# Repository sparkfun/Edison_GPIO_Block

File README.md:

SparkFun Edison GPIO Breakout
=============================

[*SparkFun Edison GPIO Breakout(DEV-13038)*](https://www.sparkfun.com/products/13038)

The GPIO Breakout is a simple breakout board to bring the GPIO from the Intel Edison to the user.  Bread board friendly, the GPIO provides level-shifted access to all basic GPIO, PWM, and UART2. GPIO may be set to VSYS or 3.3v levels. The GPIO Breakout also provides access to all three power rails found on the Intel Edison.  3.3v, 1.8v, VSYS, and GND are accessable for bread board prototyping.

Repository Contents
-------------------
* **/Hardware** - All Eagle design files (.brd, .sch)
* **/Production** - TEst bed files and production panel files

License Information
-------------------

The hardware is released under [Creative Commons ShareAlike 4.0 International](https://creativecommons.org/licenses/by-sa/4.0/).
The code is beerware; if you see me (or any other SparkFun employee) at the local, and you've found our code helpful, please buy us a round!

Distributed as-is; no warranty is given.

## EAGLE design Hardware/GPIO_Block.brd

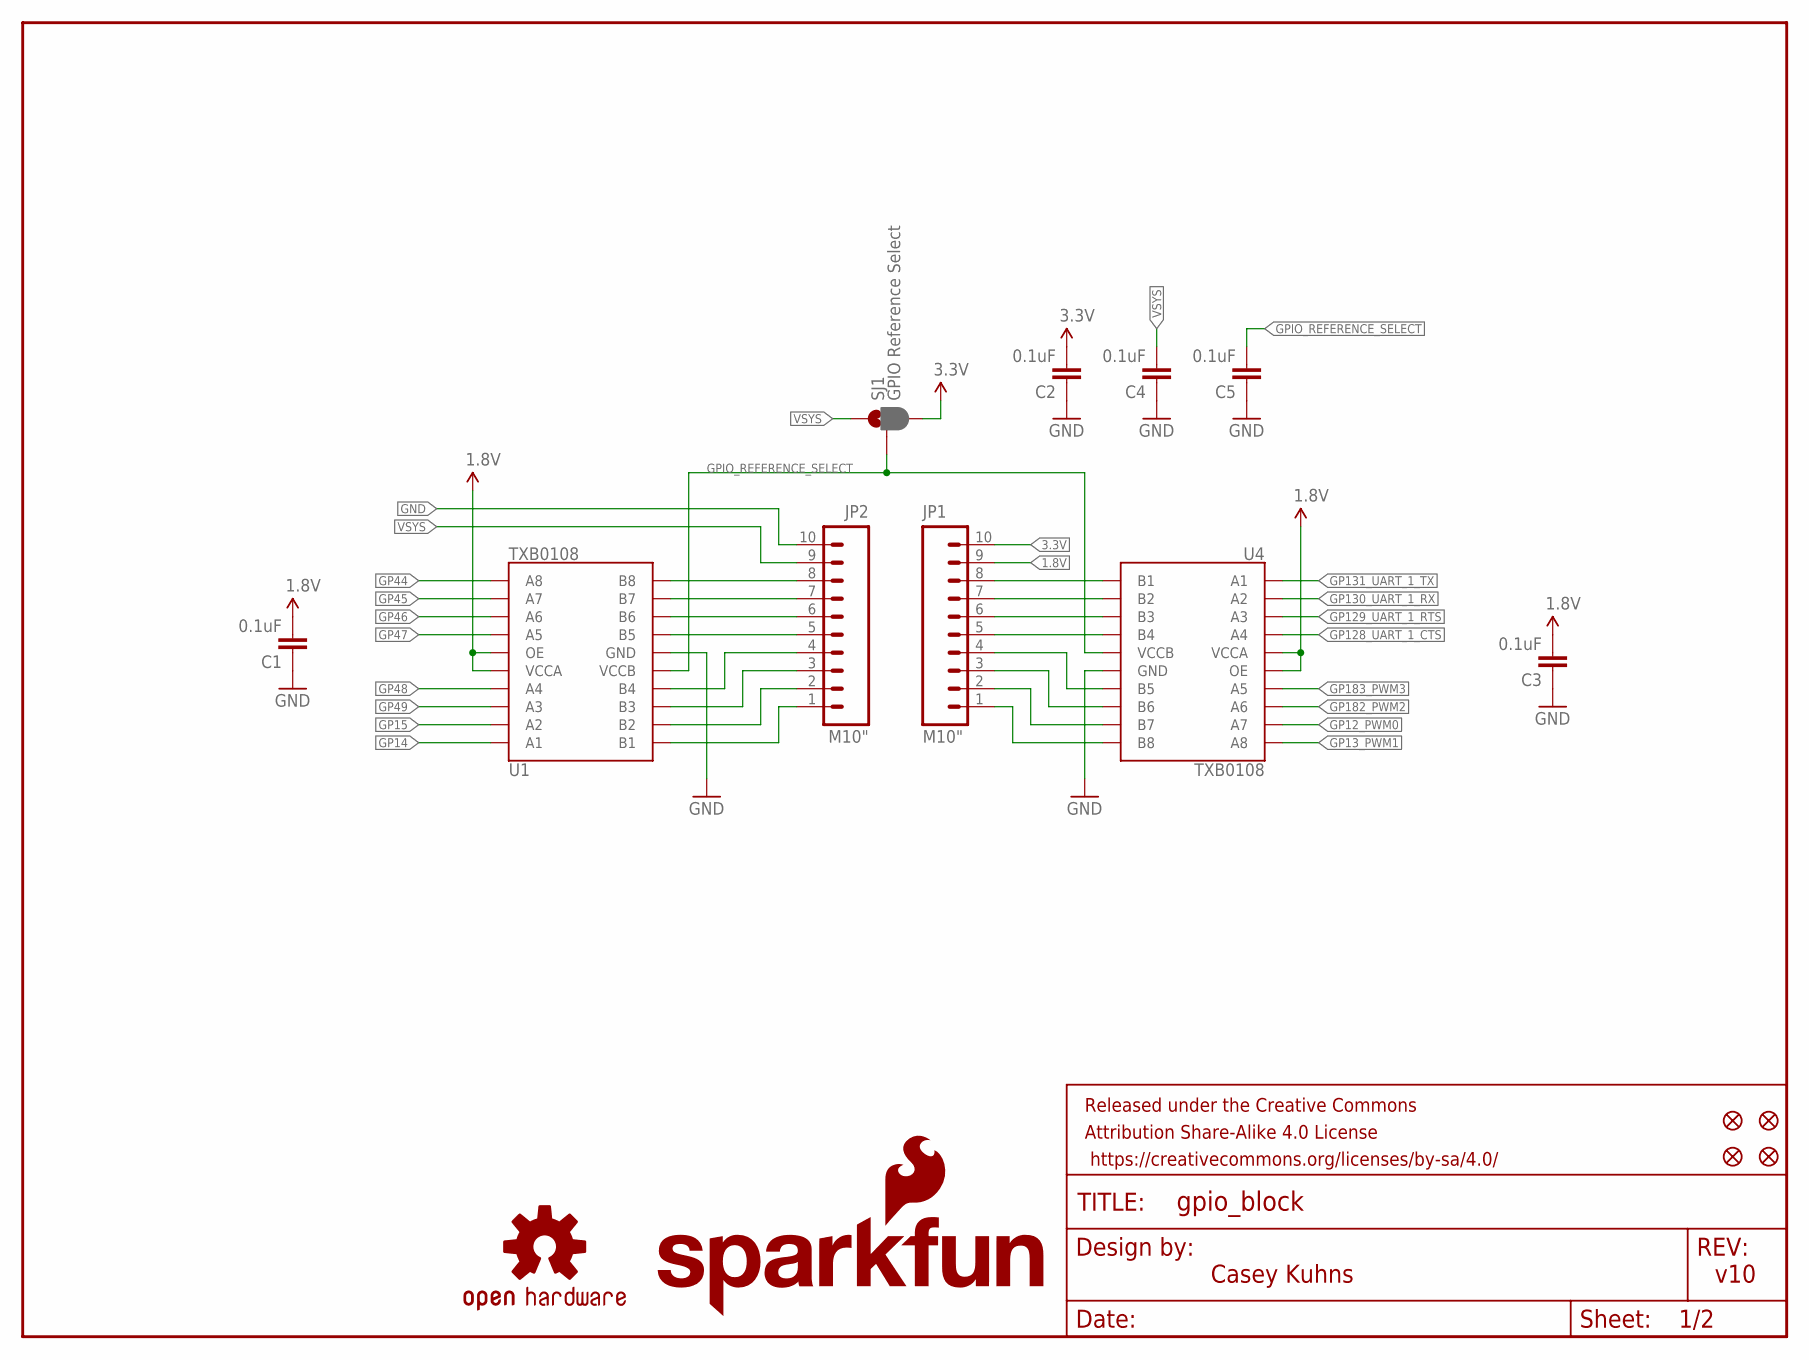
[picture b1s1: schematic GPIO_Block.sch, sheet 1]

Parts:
C1, C2, C3, C4, C5: 0.1uF; 0603-CAP
FID1, FID2, FID3, FID4: FIDUCIAL1X2; FIDUCIAL-1X2
FRAME1: FRAME-LETTER; CREATIVE_COMMONS
JP1, JP2: M10"; 1X10
LOGO1: OSHW-LOGOS; OSHW-LOGO-S
LOGO4: SFE_LOGO_NAME_FLAME.1_INCH; SFE_LOGO_NAME_FLAME_.1
SJ1: GPIO Reference Select; PAD-JUMPER-3-2OF3_NC_BY_PASTE_YES_SILK_FULL_BOX
U1, U4: TXB0108; UFDFN-20

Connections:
1.8V: C1.2, C3.2, JP1.9, U1.5 (VCCA), U1.6 (OE), U4.5 (VCCA), U4.6 (OE); also elsewhere on the board
3.3V: C2.2, JP1.10, SJ1.3; also elsewhere on the board
GND: C1.1, C2.1, C3.1, C4.1, C5.1, JP2.10, U1.15 (GND), U4.15 (GND); also elsewhere on the board
GP12_PWM0: U4.9 (A7); also elsewhere on the board
GP13_PWM1: U4.10 (A8); also elsewhere on the board
GP14: U1.1 (A1); also elsewhere on the board
GP15: U1.2 (A2); also elsewhere on the board
GP44: U1.10 (A8); also elsewhere on the board
GP45: U1.9 (A7); also elsewhere on the board
GP46: U1.8 (A6); also elsewhere on the board
GP47: U1.7 (A5); also elsewhere on the board
GP48: U1.4 (A4); also elsewhere on the board
GP49: U1.3 (A3); also elsewhere on the board
GP128_UART_1_CTS: U4.4 (A4); also elsewhere on the board
GP129_UART_1_RTS: U4.3 (A3); also elsewhere on the board
GP130_UART_1_RX: U4.2 (A2); also elsewhere on the board
GP131_UART_1_TX: U4.1 (A1); also elsewhere on the board
GP182_PWM2: U4.8 (A6); also elsewhere on the board
GP183_PWM3: U4.7 (A5); also elsewhere on the board
GPIO_REFERENCE_SELECT: C5.2, SJ1.2, U1.16 (VCCB), U4.16 (VCCB)
unnamed: JP2.8, U1.11 (B8)
unnamed: JP2.7, U1.12 (B7)
unnamed: JP2.6, U1.13 (B6)
unnamed: JP2.5, U1.14 (B5)
unnamed: JP2.4, U1.17 (B4)
unnamed: JP2.3, U1.18 (B3)
unnamed: JP2.2, U1.19 (B2)
unnamed: JP2.1, U1.20 (B1)
unnamed: JP1.4, U4.14 (B5)
unnamed: JP1.3, U4.13 (B6)
unnamed: JP1.2, U4.12 (B7)
unnamed: JP1.1, U4.11 (B8)
unnamed: JP1.5, U4.17 (B4)
unnamed: JP1.6, U4.18 (B3)
unnamed: JP1.7, U4.19 (B2)
unnamed: JP1.8, U4.20 (B1)
VSYS: C4.2, JP2.9, SJ1.1; also elsewhere on the board

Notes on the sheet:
v10
Casey Kuhns

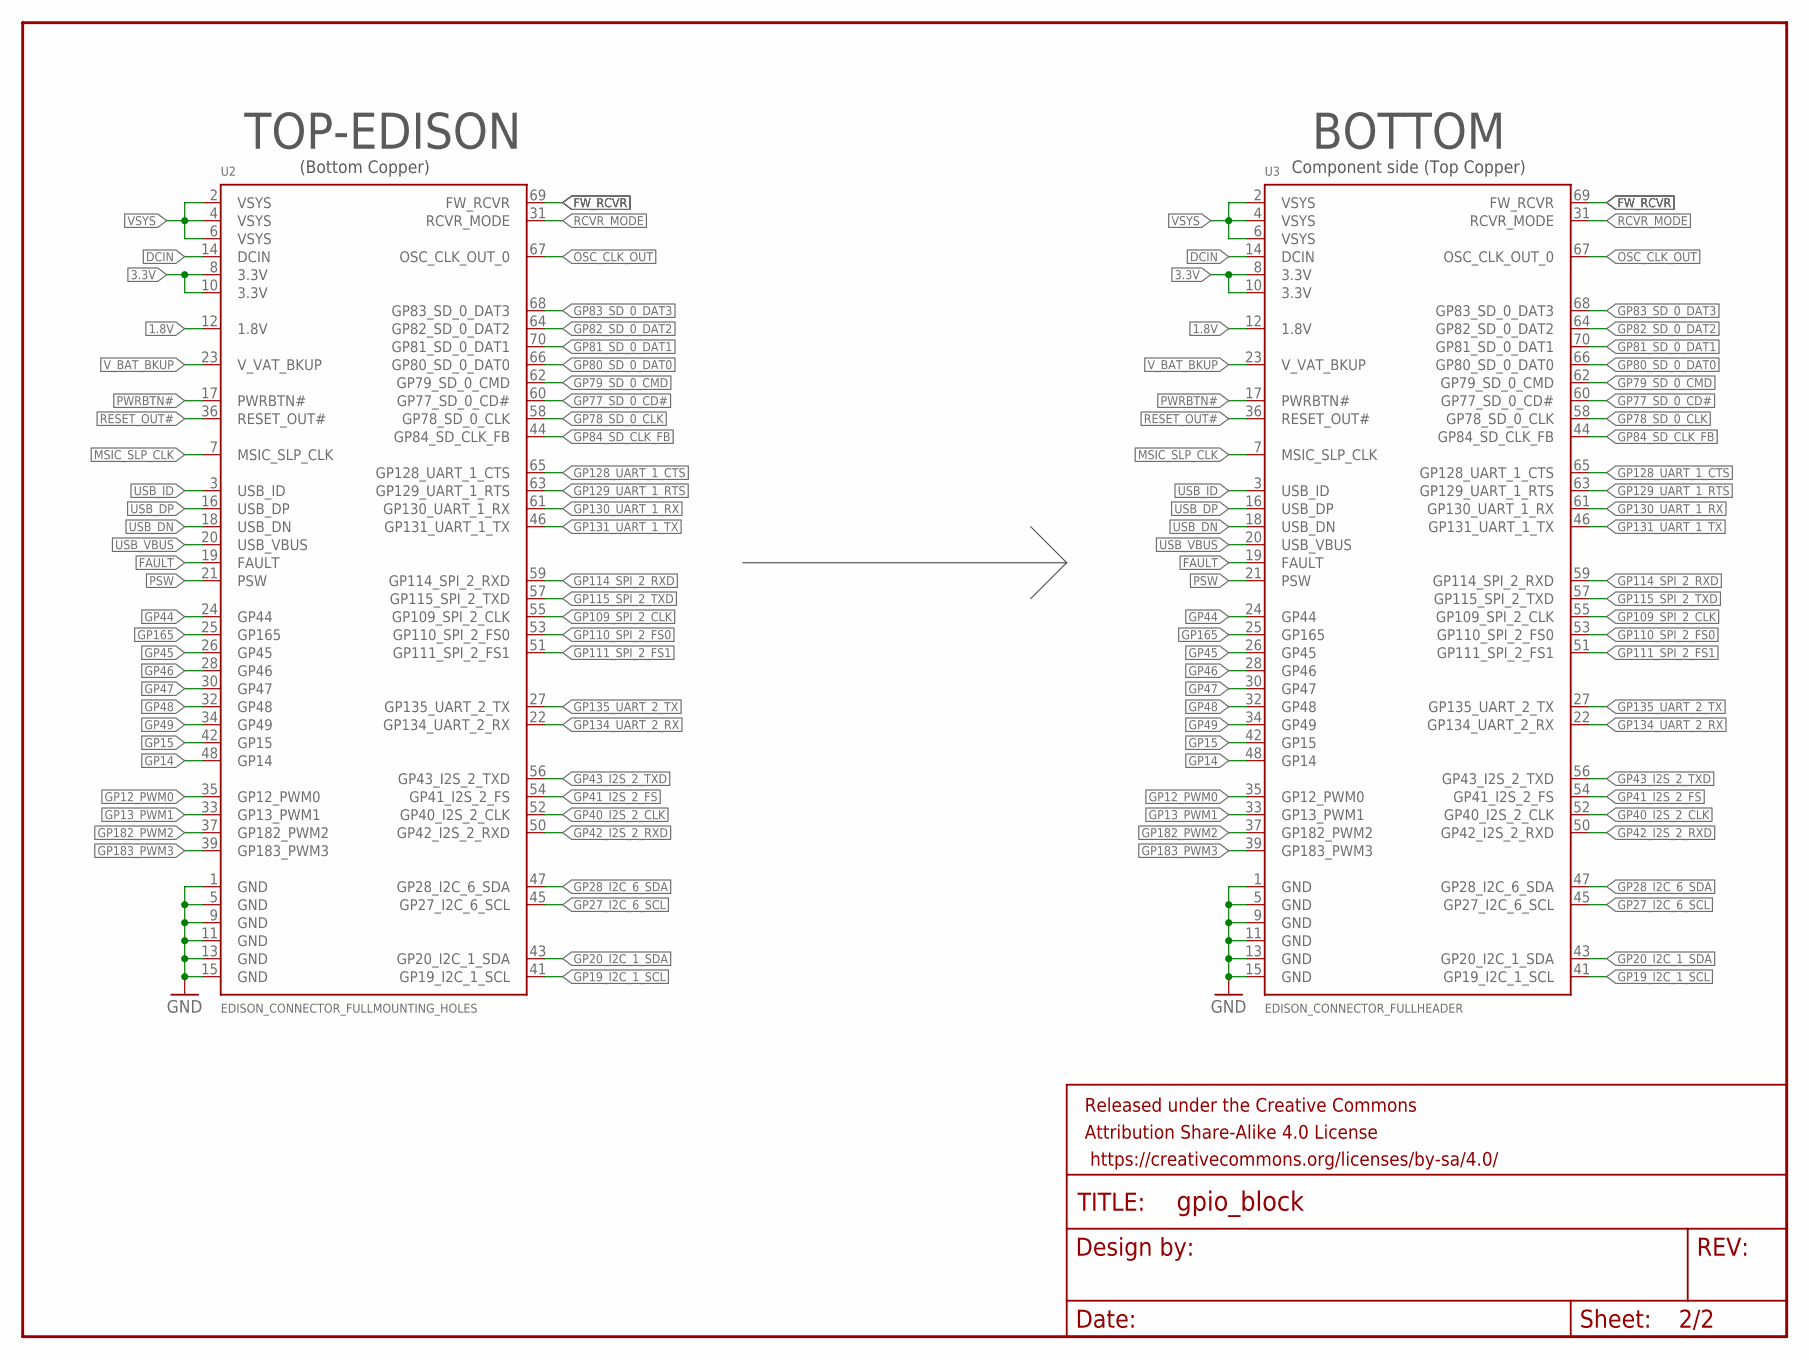
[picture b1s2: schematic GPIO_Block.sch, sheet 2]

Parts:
FRAME2: FRAME-LETTER; CREATIVE_COMMONS
U2: EDISON_CONNECTOR_FULLMOUNTING_HOLES; EDISON_DAUGHTER
U3: EDISON_CONNECTOR_FULLHEADER; DF40C-70DP-0.4(51)

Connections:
1.8V: U2.12 (1.8V), U3.12 (1.8V); also elsewhere on the board
3.3V: U2.8 (3.3V), U2.10 (3.3V), U3.8 (3.3V), U3.10 (3.3V); also elsewhere on the board
DCIN: U2.14 (DCIN), U3.14 (DCIN)
FAULT: U2.19 (FAULT), U3.19 (FAULT)
FW_RCVR: U2.69 (FW_RCVR), U3.69 (FW_RCVR)
GND: U2.1 (GND), U2.5 (GND), U2.9 (GND), U2.11 (GND), U2.13 (GND), U2.15 (GND), U3.1 (GND), U3.5 (GND), U3.9 (GND), U3.11 (GND), U3.13 (GND), U3.15 (GND); also elsewhere on the board
GP12_PWM0: U2.35 (GP12_PWM0), U3.35 (GP12_PWM0); also elsewhere on the board
GP13_PWM1: U2.33 (GP13_PWM1), U3.33 (GP13_PWM1); also elsewhere on the board
GP14: U2.48 (GP14), U3.48 (GP14); also elsewhere on the board
GP15: U2.42 (GP15), U3.42 (GP15); also elsewhere on the board
GP19_I2C_1_SCL: U2.41 (GP19_I2C_1_SCL), U3.41 (GP19_I2C_1_SCL)
GP20_I2C_1_SDA: U2.43 (GP20_I2C_1_SDA), U3.43 (GP20_I2C_1_SDA)
GP27_I2C_6_SCL: U2.45 (GP27_I2C_6_SCL), U3.45 (GP27_I2C_6_SCL)
GP28_I2C_6_SDA: U2.47 (GP28_I2C_6_SDA), U3.47 (GP28_I2C_6_SDA)
GP40_I2S_2_CLK: U2.52 (GP40_I2S_2_CLK), U3.52 (GP40_I2S_2_CLK)
GP41_I2S_2_FS: U2.54 (GP41_I2S_2_FS), U3.54 (GP41_I2S_2_FS)
GP42_I2S_2_RXD: U2.50 (GP42_I2S_2_RXD), U3.50 (GP42_I2S_2_RXD)
GP43_I2S_2_TXD: U2.56 (GP43_I2S_2_TXD), U3.56 (GP43_I2S_2_TXD)
GP44: U2.24 (GP44), U3.24 (GP44); also elsewhere on the board
GP45: U2.26 (GP45), U3.26 (GP45); also elsewhere on the board
GP46: U2.28 (GP46), U3.28 (GP46); also elsewhere on the board
GP47: U2.30 (GP47), U3.30 (GP47); also elsewhere on the board
GP48: U2.32 (GP48), U3.32 (GP48); also elsewhere on the board
GP49: U2.34 (GP49), U3.34 (GP49); also elsewhere on the board
GP77_SD_0_CD#: U2.60 (GP77_SD_0_CD#), U3.60 (GP77_SD_0_CD#)
GP78_SD_0_CLK: U2.58 (GP78_SD_0_CLK), U3.58 (GP78_SD_0_CLK)
GP79_SD_0_CMD: U2.62 (GP79_SD_0_CMD), U3.62 (GP79_SD_0_CMD)
GP80_SD_0_DAT0: U2.66 (GP80_SD_0_DAT0), U3.66 (GP80_SD_0_DAT0)
GP81_SD_0_DAT1: U2.70 (GP81_SD_0_DAT1), U3.70 (GP81_SD_0_DAT1)
GP82_SD_0_DAT2: U2.64 (GP82_SD_0_DAT2), U3.64 (GP82_SD_0_DAT2)
GP83_SD_0_DAT3: U2.68 (GP83_SD_0_DAT3), U3.68 (GP83_SD_0_DAT3)
GP84_SD_CLK_FB: U2.44 (GP84_SD_CLK_FB), U3.44 (GP84_SD_CLK_FB)
GP109_SPI_2_CLK: U2.55 (GP109_SPI_2_CLK), U3.55 (GP109_SPI_2_CLK)
GP110_SPI_2_FS0: U2.53 (GP110_SPI_2_FS0), U3.53 (GP110_SPI_2_FS0)
GP111_SPI_2_FS1: U2.51 (GP111_SPI_2_FS1), U3.51 (GP111_SPI_2_FS1)
GP114_SPI_2_RXD: U2.59 (GP114_SPI_2_RXD), U3.59 (GP114_SPI_2_RXD)
GP115_SPI_2_TXD: U2.57 (GP115_SPI_2_TXD), U3.57 (GP115_SPI_2_TXD)
GP128_UART_1_CTS: U2.65 (GP128_UART_1_CTS), U3.65 (GP128_UART_1_CTS); also elsewhere on the board
GP129_UART_1_RTS: U2.63 (GP129_UART_1_RTS), U3.63 (GP129_UART_1_RTS); also elsewhere on the board
GP130_UART_1_RX: U2.61 (GP130_UART_1_RX), U3.61 (GP130_UART_1_RX); also elsewhere on the board
GP131_UART_1_TX: U2.46 (GP131_UART_1_TX), U3.46 (GP131_UART_1_TX); also elsewhere on the board
GP134_UART_2_RX: U2.22 (GP134_UART_2_RX), U3.22 (GP134_UART_2_RX)
GP135_UART_2_TX: U2.27 (GP135_UART_2_TX), U3.27 (GP135_UART_2_TX)
GP165: U2.25 (GP165), U3.25 (GP165)
GP182_PWM2: U2.37 (GP182_PWM2), U3.37 (GP182_PWM2); also elsewhere on the board
GP183_PWM3: U2.39 (GP183_PWM3), U3.39 (GP183_PWM3); also elsewhere on the board
MSIC_SLP_CLK: U2.7 (MSIC_SLP_CLK), U3.7 (MSIC_SLP_CLK)
OSC_CLK_OUT: U2.67 (OSC_CLK_OUT_0), U3.67 (OSC_CLK_OUT_0)
PSW: U2.21 (PSW), U3.21 (PSW)
PWRBTN#: U2.17 (PWRBTN#), U3.17 (PWRBTN#)
RCVR_MODE: U2.31 (RCVR_MODE), U3.31 (RCVR_MODE)
RESET_OUT#: U2.36 (RESET_OUT#), U3.36 (RESET_OUT#)
USB_DN: U2.18 (USB_DN), U3.18 (USB_DN)
USB_DP: U2.16 (USB_DP), U3.16 (USB_DP)
USB_ID: U2.3 (USB_ID), U3.3 (USB_ID)
USB_VBUS: U2.20 (USB_VBUS), U3.20 (USB_VBUS)
VSYS: U2.2 (VSYS), U2.4 (VSYS), U2.6 (VSYS), U3.2 (VSYS), U3.4 (VSYS), U3.6 (VSYS); also elsewhere on the board
V_BAT_BKUP: U2.23 (V_VAT_BKUP), U3.23 (V_VAT_BKUP)

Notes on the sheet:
TOP-EDISON
BOTTOM
Component side (Top Copper)
(Bottom Copper)

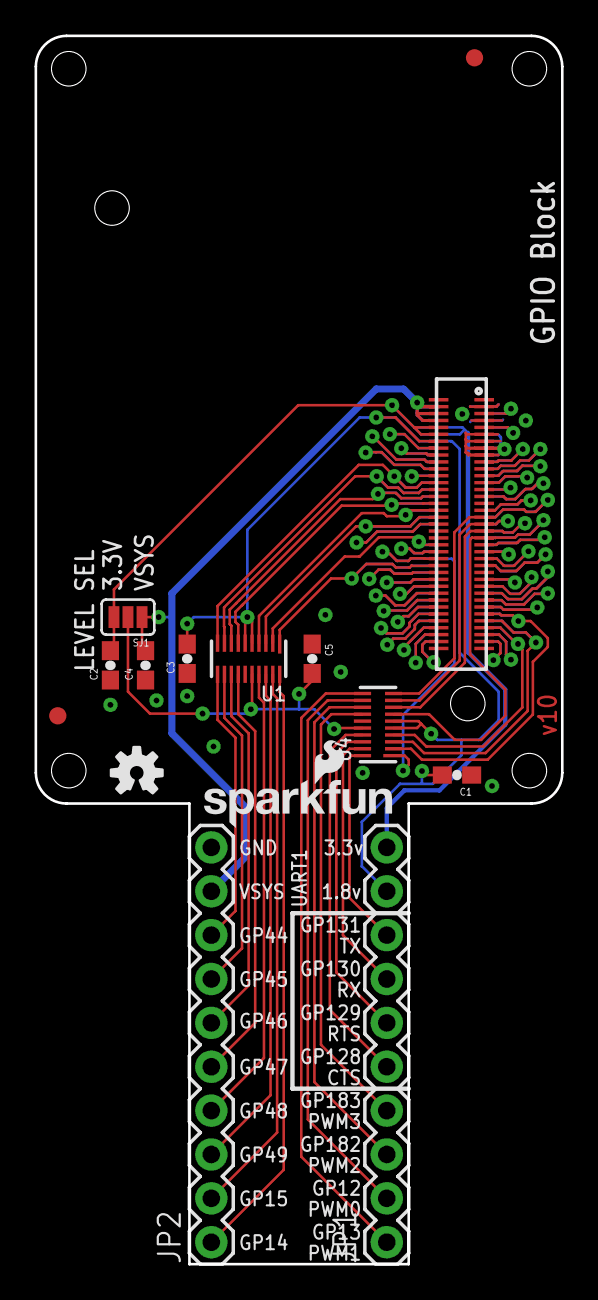
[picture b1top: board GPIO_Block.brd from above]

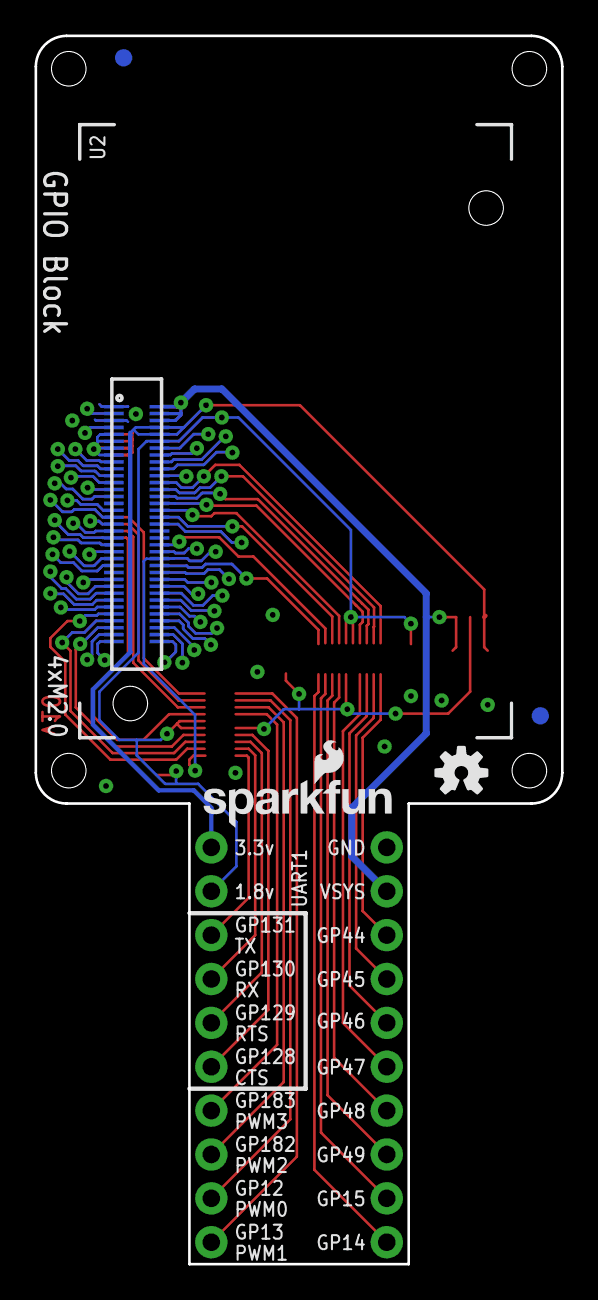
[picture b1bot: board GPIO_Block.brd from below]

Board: 2 copper layers, 30.5 x 71.1 mm, 22 parts (6 on the bottom side), 75 nets.

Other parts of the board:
LOGO2: OSHW-LOGOS; OSHW-LOGO-S
LOGO3: SFE_LOGO_NAME_FLAME.1_INCH; SFE_LOGO_NAME_FLAME_.1

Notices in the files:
parts and their libraries:
SparkFun-Aesthetics: Licensing: Creative Commons ShareAlike 4.0 International - https://creativecommons.org/licenses/by-sa/4.0
SparkFun-Aesthetics: Released under the Creative Commons Attribution Share-Alike 4.0 License
SparkFun-Aesthetics: Released under the Creative Commons
